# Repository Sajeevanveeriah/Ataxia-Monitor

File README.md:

# Ataxia Device and Monitor

This repository contains the VW-MTC1 MazeTrack controller design, its LTspice analysis tools, and the Android monitoring prototype. The controller package is the current hardware setup. The Android app still reads phone sensors; a board-to-app transport and executable board firmware have not been implemented.

## Project map

| Path | Contents |
| --- | --- |
| `VW-MTC1/Hardware/` | KiCad 10 sources, fabrication exports and archived ERC/DRC reports |
| `VW-MTC1/Firmware/` | ESP32-S3 pin-map header; no flashable firmware application yet |
| `VW-MTC1/Simulation/` | LTspice circuits, archived results/plots and Python analysis tools |
| `VW-MTC1/Docs/` | Original Rev00 design report, datasheet and images |
| `app/` | Android app, local JVM tests and [app documentation](app/README.md) |
| `tests/` | Python unit tests using synthetic waveforms and mocked simulator processes |
| `scripts/check_project.py` | Rebuild generated schematics and summary in `build/` |

The board has not been physically built or measured. Saved simulation and CAD reports are historical evidence, not a fresh hardware acceptance result. See [VW-MTC1/README.md](VW-MTC1/README.md) and the design report for outstanding engineering checks.

## Python build and tests from a clean checkout

Use Python 3.12 or newer. The development dependency set is pinned in `requirements-dev.txt`. NumPy 2 or newer is required because the analysis uses `numpy.trapezoid`.

Windows PowerShell:

```powershell
python -m venv .venv
.\.venv\Scripts\python.exe -m pip install -r requirements-dev.txt
.\.venv\Scripts\python.exe -m pip install --no-build-isolation -e .
.\.venv\Scripts\python.exe -m pytest -q
.\.venv\Scripts\python.exe -m build --no-isolation
.\.venv\Scripts\python.exe scripts/check_project.py
```

Linux/macOS:

```sh
python3 -m venv .venv
.venv/bin/python -m pip install -r requirements-dev.txt
.venv/bin/python -m pip install --no-build-isolation -e .
.venv/bin/python -m pytest -q
.venv/bin/python -m build --no-isolation
.venv/bin/python scripts/check_project.py
```

The build produces a Python wheel and source archive in `dist/`. It packages the tools, not the large hardware exports. The generation check writes to `build/vw-mtc1/` and preserves the supplied simulation evidence. Its summary is rebuilt from stored results; it does not claim a fresh simulation.

For line and branch coverage:

```sh
python -m pytest --cov=vw_mtc1 --cov-report=term-missing
```

Coverage reports include the full analysis scripts as well as the reusable helpers. Hardware-free unit tests do not execute every full-circuit analysis path.

A host C++ syntax check for the pin-map header is also available:

```sh
g++ -std=c++17 -Wall -Wextra -Werror -fsyntax-only tests/pinmap_compile.cpp
```

This checks header compilation only. It does not produce ESP32 firmware.

## Running LTspice

LTspice 26.1.1 was used for the supplied Rev00 evidence. Install LTspice separately, with its standard model library. No simulator is needed for the unit tests or Python package build.

The runner accepts `--executable`, then checks `LTSPICE_EXE`, `PATH` and standard Windows installation locations. It returns a failure for a timeout, a non-zero simulator exit, missing/unchanged/empty logs, simulator errors or failed measurements.

Run against a scratch copy when retaining the original logs:

```powershell
Copy-Item -Recurse VW-MTC1\Simulation\LTspice build\ltspice-run
.\.venv\Scripts\python.exe -m vw_mtc1.runlt build\ltspice-run\sim00_mosfet_model_check.cir 300
```

The source package omits raw waveform files. Regenerate the required `.cir` files before running `an_sim01` through `an_sim06_07`. Set `VW_MTC1_SIMULATION_DIR` to the scratch simulation directory containing `LTspice/`, `results.json` and, when generated, `Plots/`:

```powershell
$env:VW_MTC1_SIMULATION_DIR = (Resolve-Path build\vw-mtc1).Path
.\.venv\Scripts\python.exe -m vw_mtc1.an_sim01
```

The scripts execute sequentially when updating the same `results.json`; concurrent writers are not supported. Analysis modules should be run with `python -m vw_mtc1.<module>` after installation. A wheel installed outside this checkout also needs `VW_MTC1_SIMULATION_DIR` for data-dependent commands.

The five formerly timed-out cases completed with an 1800-second limit. Charger and
touch-gap investigations, diagnostic netlists and remaining acceptance failures are
documented in the [Rev01 verification record](docs/20261020-VW-MTC1-Verification-Rev01.md).
To reproduce the additional diagnostic sweeps:

```powershell
.\.venv\Scripts\python.exe scripts/investigate_analogue.py --output build\analogue-investigation --timeout 600
```

Simulation completion does not imply that every measurement or design target
passes. The runner also rejects failed rows in stepped measurement tables.

## Android build and tests

Use JDK 17, Android SDK platform 34 and build-tools 34.0.0. Set `JAVA_HOME` and `ANDROID_HOME` to those installations, or configure the SDK in Android Studio. The committed Gradle 8.2.1 wrapper verifies its distribution checksum.

```powershell
.\gradlew.bat assembleDebug testDebugUnitTest lintDebug
```

On Linux/macOS, use `./gradlew` with the same tasks. The debug APK is written to `app/build/outputs/apk/debug/`. JVM tests mock Android sensors and Room boundaries; they do not require a phone or emulator. Device instrumentation and physical sensor validation remain separate checks.

The app preserves raw phone proximity readings in their own sensor type. They are not calibrated along-maze distance. External board samples need an explicit transport and calibration contract before they can drive distance/offset fusion.

## Automated verification

The PR workflow builds and tests the Python tools on Windows and Linux, checks the pin-map header on Linux, and builds/tests/lints Android on Linux. It does not flash hardware, run physical measurements or regenerate fabrication exports.

The original thesis and previously delivered package ZIP remain local and are excluded from Git. The original Rev00 package files under `VW-MTC1/` remain available alongside the maintained source tools.

## Project handoff

Read the [project handoff](HANDOFF.md) for current work, checks and the next step.

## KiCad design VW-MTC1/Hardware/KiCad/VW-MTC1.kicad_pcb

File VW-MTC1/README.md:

# Voltwyn VW-MTC1 MazeTrack Controller - Rev A (Rev00 package, 19 October 2026)

Replacement controller board for the SEJ446 wire-maze ataxia assessment rig.

| Folder | Contents |
|---|---|
| `Docs/` | Datasheet PDF, design report PDF, schematic PDF, `Images/` (3D renders, layer plots, schematic PNGs) |
| `Hardware/KiCad/` | KiCad 10 project (open `VW-MTC1.kicad_pro`); custom symbol `Voltwyn.kicad_sym`, custom rules `VW-MTC1.kicad_dru` |
| `Hardware/Fabrication/` | Gerbers + drill (ZIP), BOM (CSV), pick-and-place (CSV), STEP 3D model |
| `Hardware/Reports/` | KiCad ERC and DRC reports |
| `Simulation/` | LTspice netlists and `.asc` schematics, plots, `results.json`, `Simulation_Summary.md` (raw waveform files not included: re-run the `.cir` files in LTspice to regenerate) |
| `Firmware/` | `vw_mtc1_pins.h` ESP32-S3 pin map |

Status: design complete, ERC 0 errors, DRC 0 errors / 0 unconnected / 0 schematic-parity issues.
Not yet built or measured. See the open items in section 10 of the design report before ordering.
Research and education use only; not a registered medical device.

The table and status above describe the original Rev00 design package. The maintained
Python tools now have a package build and hardware-free regression suite. See the
[repository build instructions](../README.md) and
[latest verification record](../docs/20261020-VW-MTC1-Verification-Rev01.md).
`Firmware/` still contains a pin-map header only, not a flashable firmware application.

## Project handoff

Read the [project handoff](../HANDOFF.md) for current work, checks and the next step.

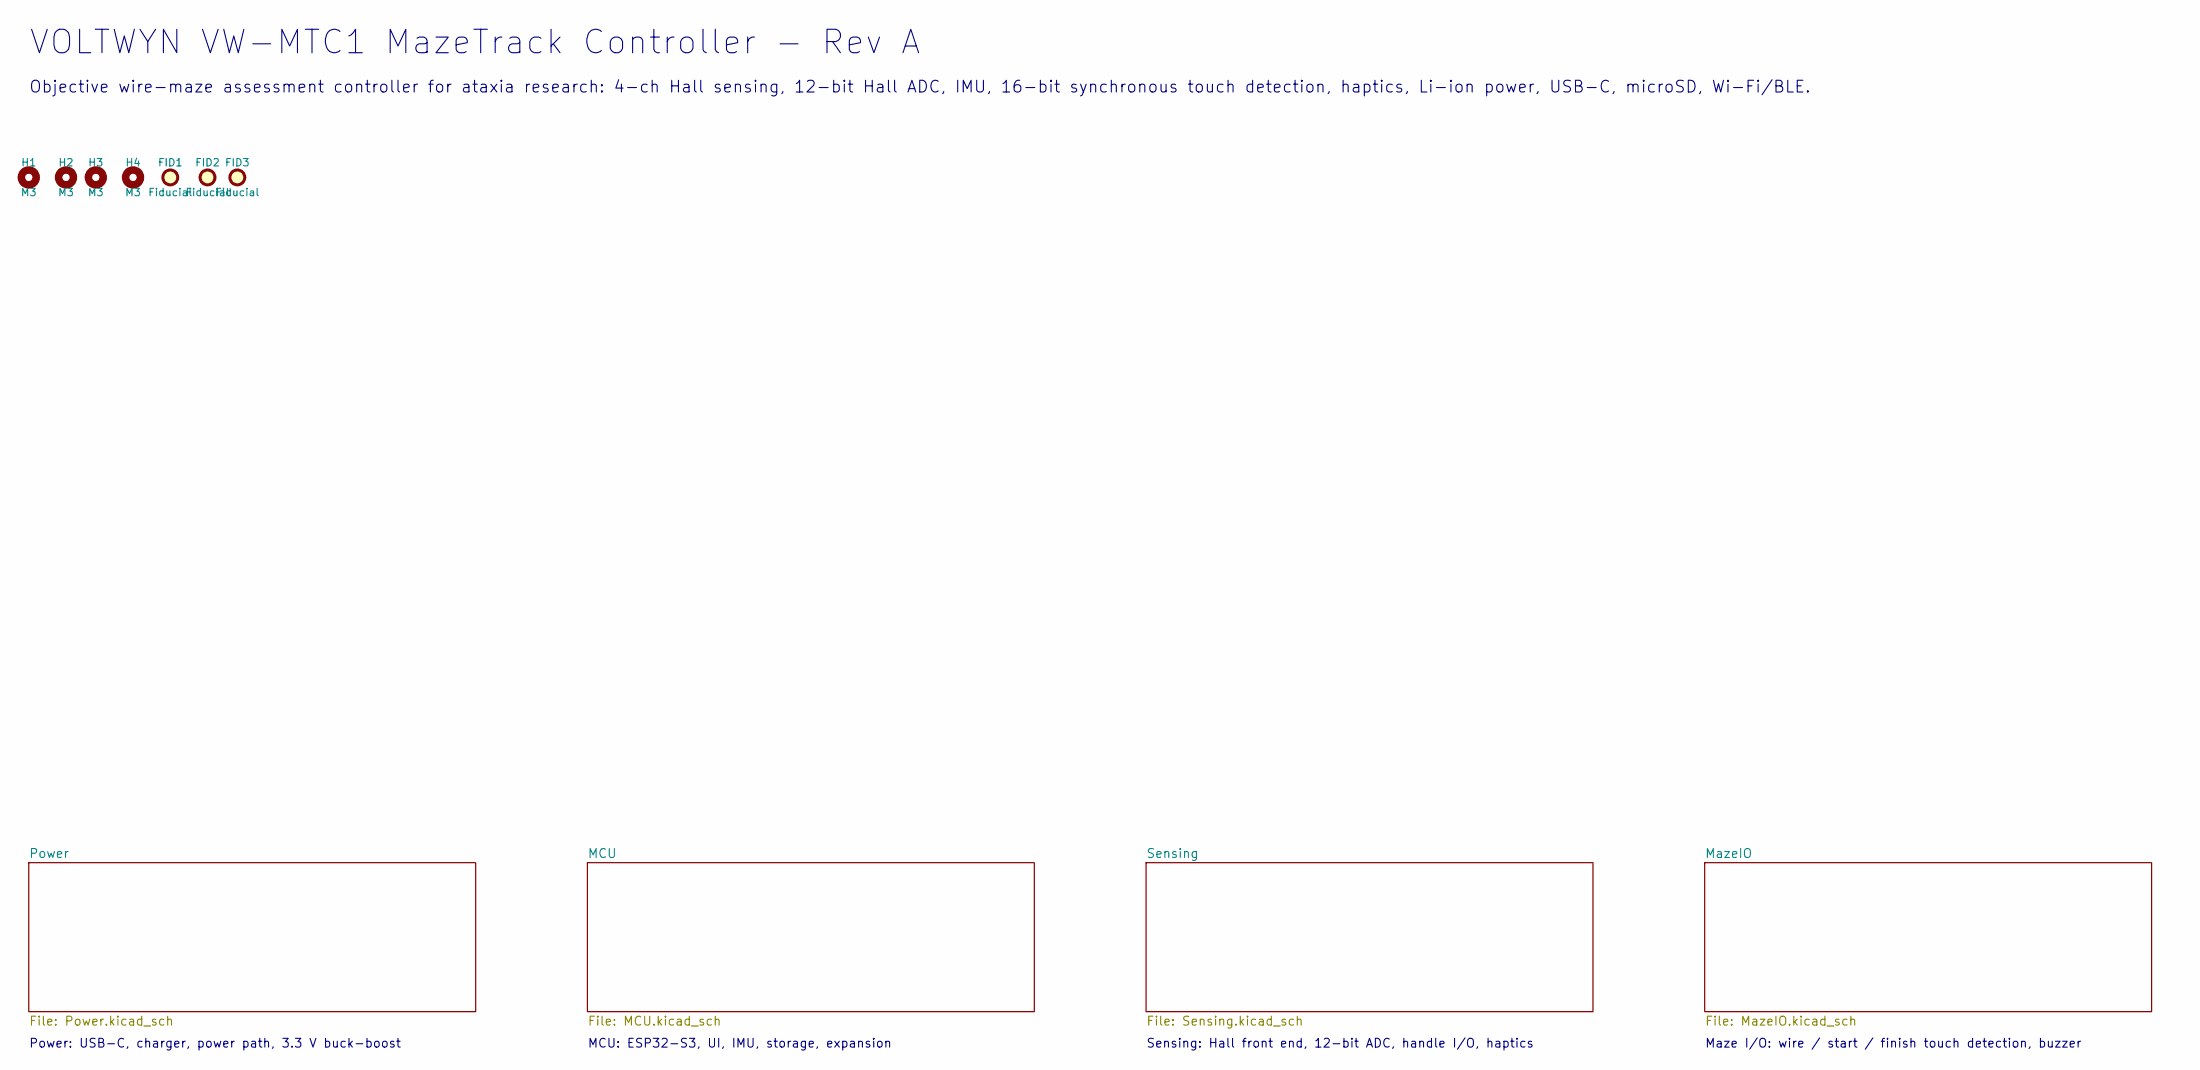
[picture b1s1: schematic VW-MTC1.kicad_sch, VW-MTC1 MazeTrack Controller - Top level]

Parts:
FID1, FID2, FID3: Fiducial; Fiducial_1mm_Mask2mm
H1, H2, H3, H4: M3; MountingHole_3.2mm_M3

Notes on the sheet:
VOLTWYN VW-MTC1 MazeTrack Controller - Rev A
Objective wire-maze assessment controller for ataxia research: 4-ch Hall sensing, 12-bit Hall ADC, IMU, 16-bit synchronous touch detection, haptics, Li-ion power, USB-C, microSD, Wi-Fi/BLE.
Power: USB-C, charger, power path, 3.3 V buck-boost
MCU: ESP32-S3, UI, IMU, storage, expansion
Sensing: Hall front end, 12-bit ADC, handle I/O, haptics
Maze I/O: wire / start / finish touch detection, buzzer

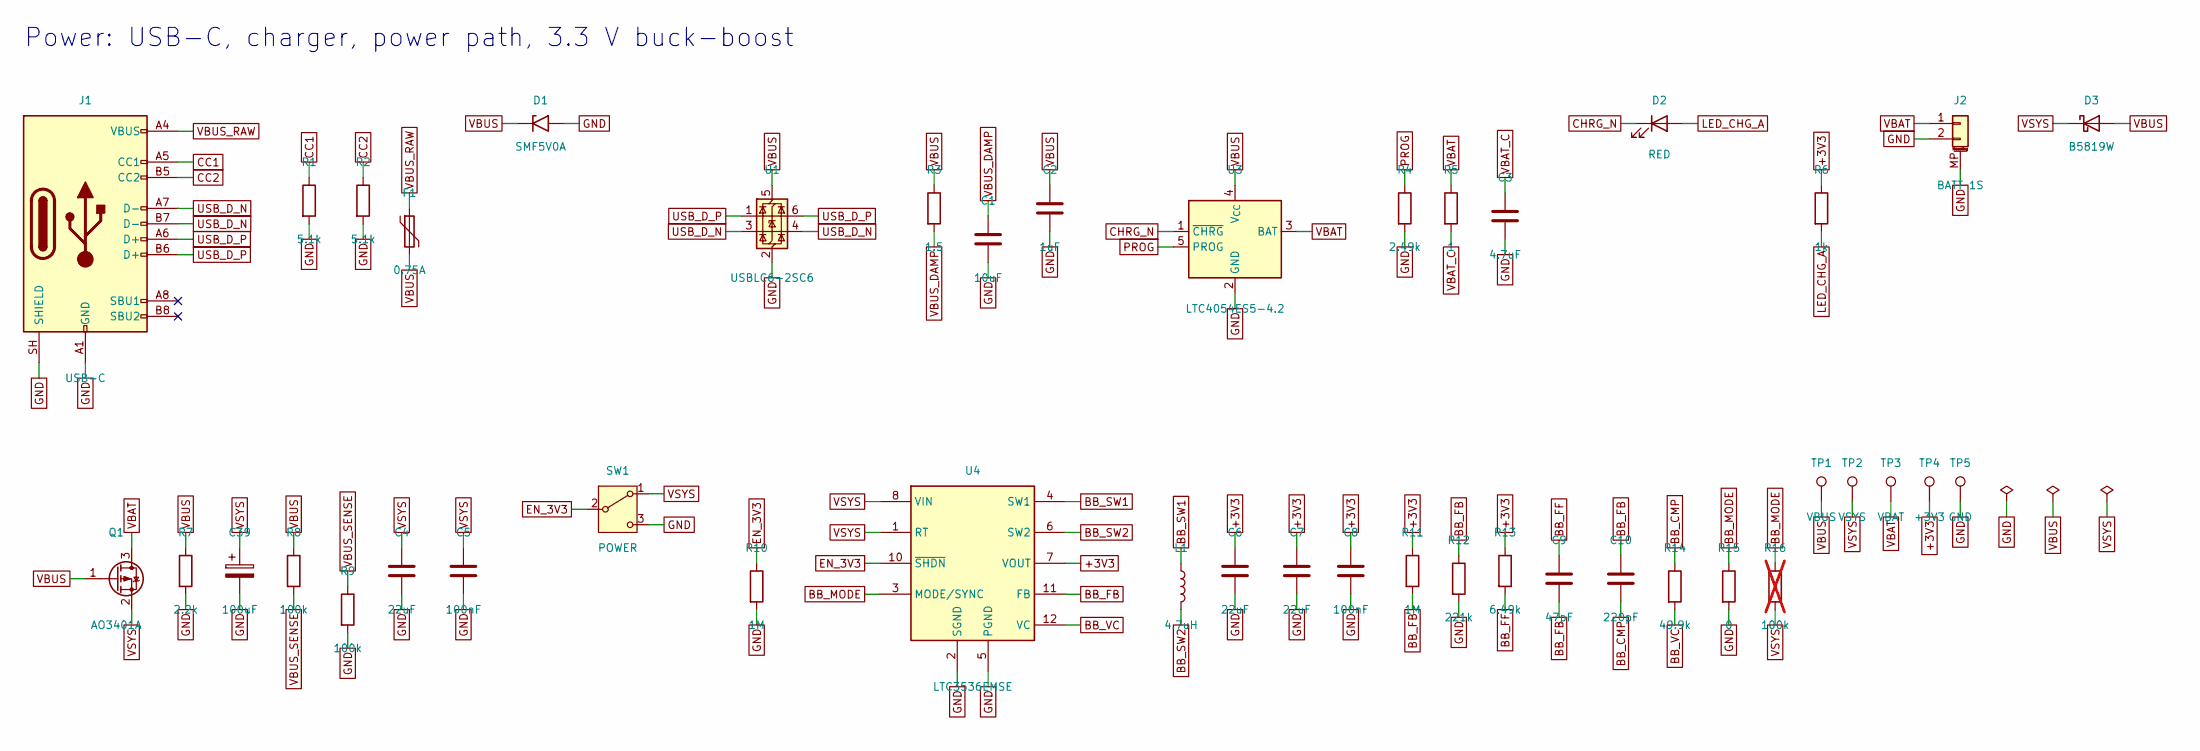
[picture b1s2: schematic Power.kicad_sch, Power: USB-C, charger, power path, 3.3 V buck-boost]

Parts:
C1: 10uF; C_0805_2012Metric; MPN GRM21BR61E106KA73L
C2: 1uF; C_0603_1608Metric; MPN GRM188R61E105KA12D
C3: 4.7uF; C_0805_2012Metric; MPN GRM21BR61C475KA88L
C4, C6, C7: 22uF; C_0805_2012Metric; MPN GRM21BR61A226ME44L
C5, C8: 100nF; C_0603_1608Metric; MPN GRM188R71H104KA93D
C9: 47pF; C_0603_1608Metric; MPN GRM1885C1H470JA01D
C10: 220pF; C_0603_1608Metric; MPN GRM1885C1H221JA01D
C39: 100uF; CP_EIA-3528-21_Kemet-B; MPN T520B107M006ATE070
D1: SMF5V0A; D_SMF; MPN SMF5V0A
D2: RED; LED_0603_1608Metric; MPN 150060RS75000
D3: B5819W; D_SOD-123; MPN B5819W
F1: 0.75A; Fuse_1206_3216Metric; MPN 1206L075THYR
J1: USB-C; USB_C_Receptacle_GCT_USB4105-xx-A_16P_TopMnt_Horizontal; MPN USB4105-GF-A
J2: BATT 1S; JST_PH_S2B-PH-SM4-TB_1x02-1MP_P2.00mm_Horizontal; MPN S2B-PH-SM4-TB(LF)(SN)
L1: 4.7uH; L_Coilcraft_XxL4020; MPN XFL4020-472MEC
Q1: AO3401A; SOT-23; MPN AO3401A
R1, R2: 5.1k; R_0603_1608Metric; MPN RC0603FR-075R1kL
R3: 1.5; R_0603_1608Metric; MPN RC0603FR-071R5L
R4: 2.49k; R_0603_1608Metric; MPN RC0603FR-072K49L
R5: 1; R_0603_1608Metric; MPN RC0603FR-071RL
R6: 1k; R_0603_1608Metric; MPN RC0603FR-071kL
R7: 2.2k; R_0603_1608Metric; MPN RC0603FR-072R2kL
R8, R9: 100k; R_0603_1608Metric; MPN RC0603FR-07100kL
R10, R11: 1M; R_0603_1608Metric; MPN RC0603FR-071ML
R12: 221k; R_0603_1608Metric; MPN RC0603FR-07221kL
R13: 6.49k; R_0603_1608Metric; MPN RC0603FR-076R49kL
R14: 49.9k; R_0603_1608Metric; MPN RC0603FR-0749R9kL
R15: 0; R_0603_1608Metric; MPN RC0603JR-070RL
R16: 100k; R_0603_1608Metric; MPN RC0603FR-07100kL; not fitted
SW1: POWER; SW_SPDT_PCM12; MPN PCM12SMTR
TP1: VBUS; TestPoint_Pad_D1.5mm
TP2: VSYS; TestPoint_Pad_D1.5mm
TP3: VBAT; TestPoint_Pad_D1.5mm
TP4: +3V3; TestPoint_Pad_D1.5mm
TP5: GND; TestPoint_Pad_D1.5mm
U1: USBLC6-2SC6; SOT-23-6; MPN USBLC6-2SC6
U3: LTC4054ES5-4.2; TSOT-23-5; MPN LTC4054ES5-4.2#TRPBF
U4: LTC3536EMSE; MSOP-12-1EP_3x4.039mm_P0.65mm_EP1.651x2.845mm_ThermalVias; MPN LTC3536EMSE#PBF

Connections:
+3V3: C6.1, C7.1, C8.1, R6.1, R11.1, R13.1, TP4.1, U4.7 (VOUT); also elsewhere on the board
BB_CMP: C10.2, R14.1
BB_FB: C9.2, C10.1, R11.2, R12.1, U4.11 (FB)
BB_FF: C9.1, R13.2
BB_MODE: R15.1, R16.1, U4.3 (MODE/SYNC)
BB_SW1: L1.1, U4.4 (SW1)
BB_SW2: L1.2, U4.6 (SW2)
BB_VC: R14.2, U4.12 (VC)
CC1: J1.A5 (CC1), R1.1
CC2: J1.B5 (CC2), R2.1
CHRG_N: D2.1 (K), U3.1 (~CHRG); also elsewhere on the board
EN_3V3: R10.1, SW1.2 (B), U4.10 (~SHDN)
GND: C1.2, C2.2, C3.2, C4.2, C5.2, C6.2, C7.2, C8.2, C39.2, D1.2 (A2), J1.A1 (GND), J1.A12 (GND), J1.B1 (GND), J1.B12 (GND), J1.SH (SHIELD), J2.2, J2.MP (MountPin), R1.2, R2.2, R4.2, R7.2, R9.2, R10.2, R12.2, R15.2, SW1.3 (C), TP5.1, U1.2 (GND), U3.2 (GND), U4.2 (SGND), U4.5 (PGND), U4.13 (PGND); also elsewhere on the board
LED_CHG_A: D2.2 (A), R6.2
PROG: R4.1, U3.5 (PROG)
USB_D_N: J1.A7 (D-), J1.B7 (D-), U1.3 (I/O2), U1.4 (I/O2); also elsewhere on the board
USB_D_P: J1.A6 (D+), J1.B6 (D+), U1.1 (I/O1), U1.6 (I/O1); also elsewhere on the board
VBAT: J2.1, Q1.3 (D), R5.1, TP3.1, U3.3 (BAT); also elsewhere on the board
VBAT_C: C3.1, R5.2
VBUS: C2.1, D1.1 (A1), D3.2 (A), F1.2, Q1.1 (G), R3.1, R7.1, R8.1, TP1.1, U1.5 (VBUS), U3.4 (V_{CC})
VBUS_DAMP: C1.1, R3.2
VBUS_RAW: F1.1, J1.A4 (VBUS), J1.A9 (VBUS), J1.B4 (VBUS), J1.B9 (VBUS)
VBUS_SENSE: R8.2, R9.1; also elsewhere on the board
VSYS: C4.1, C5.1, C39.1, D3.1 (K), Q1.2 (S), R16.2, SW1.1 (A), TP2.1, U4.1 (RT), U4.8 (VIN), U4.9 (VIN); also elsewhere on the board

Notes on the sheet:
Power: USB-C, charger, power path, 3.3 V buck-boost

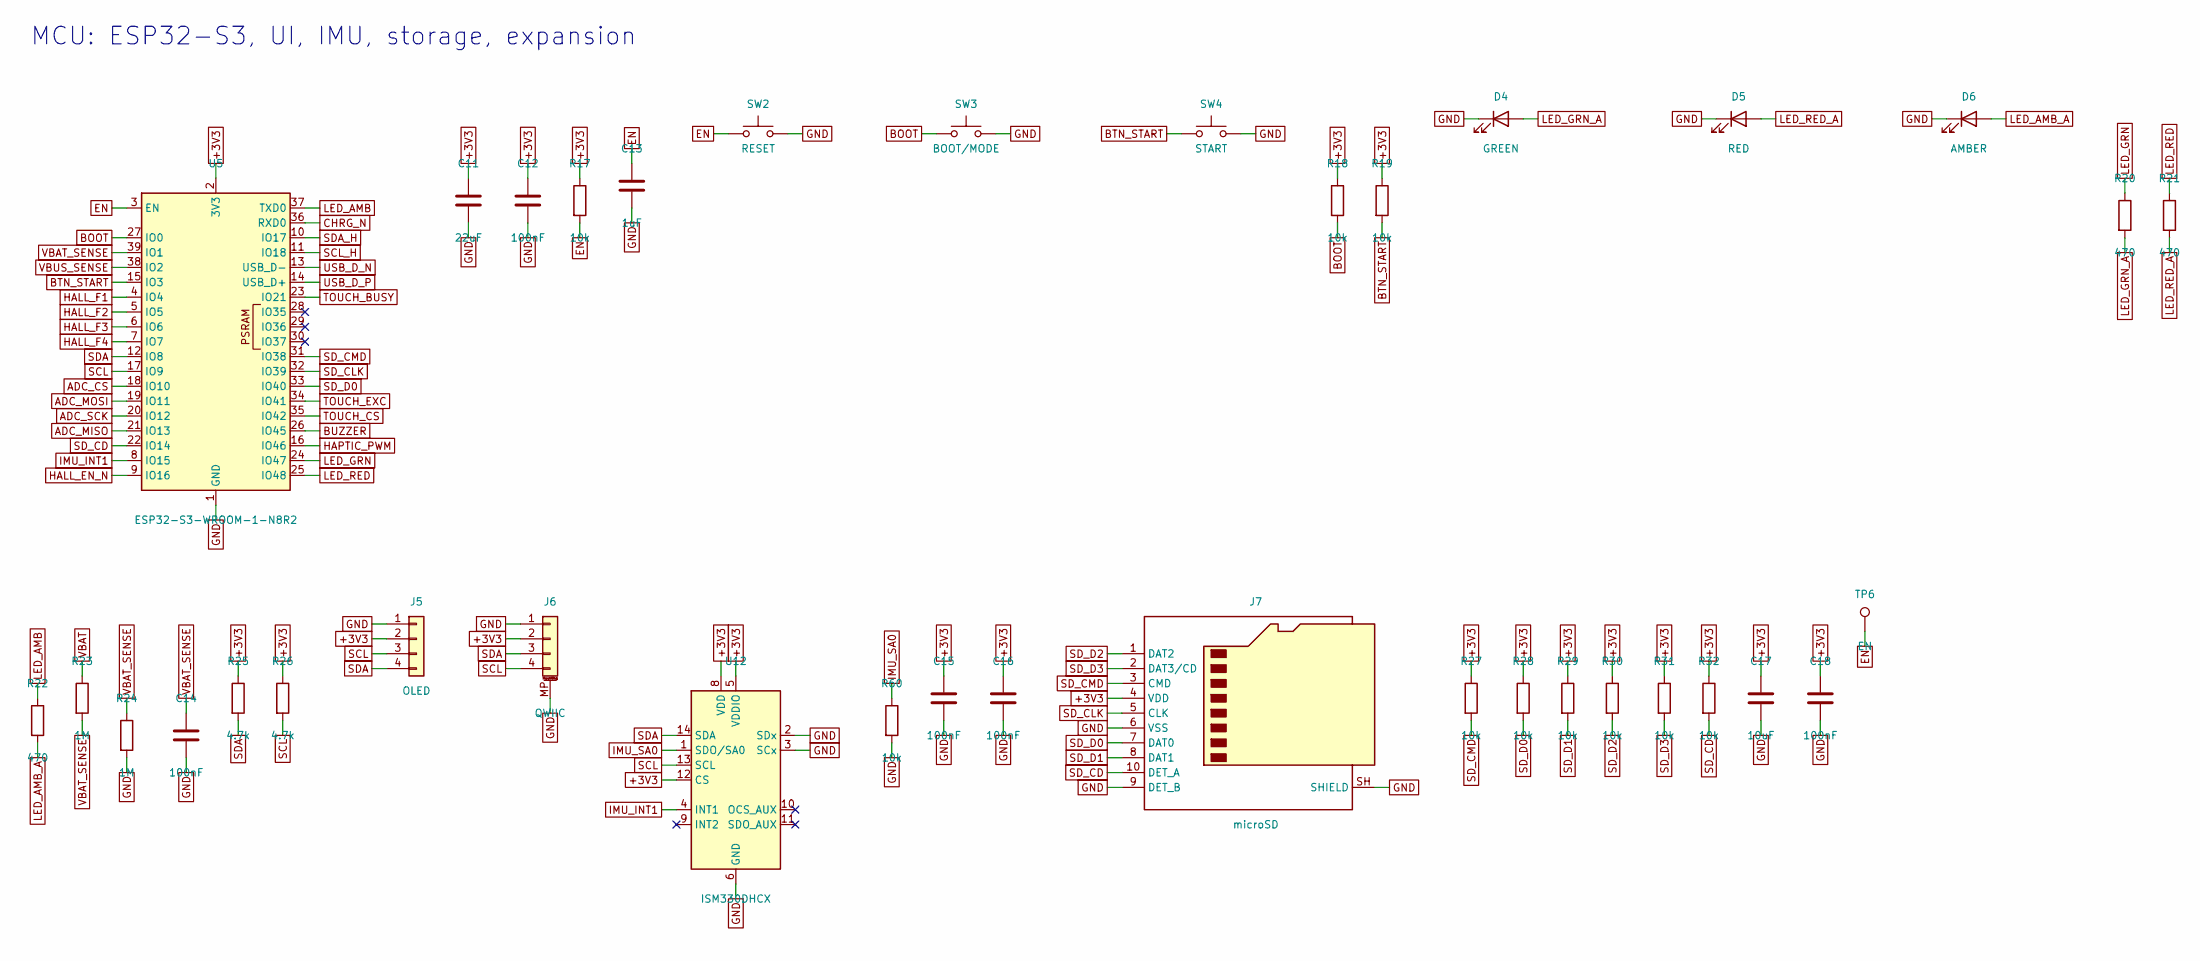
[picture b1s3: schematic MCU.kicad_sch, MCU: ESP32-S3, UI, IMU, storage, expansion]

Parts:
C11: 22uF; C_0805_2012Metric; MPN GRM21BR61A226ME44L
C12, C14, C15, C16, C18: 100nF; C_0603_1608Metric; MPN GRM188R71H104KA93D
C13: 1uF; C_0603_1608Metric; MPN GRM188R61E105KA12D
C17: 10uF; C_0805_2012Metric; MPN GRM21BR61E106KA73L
D4: GREEN; LED_0603_1608Metric; MPN 150060GS75000
D5: RED; LED_0603_1608Metric; MPN 150060RS75000
D6: AMBER; LED_0603_1608Metric; MPN 150060AS75000
J5: OLED; PinHeader_1x04_P2.54mm_Vertical; MPN PH1-04-UA
J6: QWIIC; JST_SH_SM04B-SRSS-TB_1x04-1MP_P1.00mm_Horizontal; MPN SM04B-SRSS-TB(LF)(SN)
J7: microSD; microSD_HC_Hirose_DM3AT-SF-PEJM5; MPN DM3AT-SF-PEJM5
R17, R18, R19, R27, R28, R29, R30, R31, R32, R60: 10k; R_0603_1608Metric; MPN RC0603FR-0710kL
R20, R21, R22: 470; R_0603_1608Metric; MPN RC0603FR-07470L
R23, R24: 1M; R_0603_1608Metric; MPN RC0603FR-071ML
R25, R26: 4.7k; R_0603_1608Metric; MPN RC0603FR-074R7kL
SW2: RESET; SW_SPST_TL3342; MPN TL3342F160QG
SW3: BOOT/MODE; SW_SPST_TL3342; MPN TL3342F160QG
SW4: START; SW_SPST_TL3342; MPN TL3342F160QG
TP6: EN; TestPoint_Pad_D1.5mm
U5: ESP32-S3-WROOM-1-N8R2; ESP32-S3-WROOM-1; MPN ESP32-S3-WROOM-1-N8R2
U12: ISM330DHCX; LGA-14_3x2.5mm_P0.5mm_LayoutBorder3x4y; MPN ISM330DHCXTR

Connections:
+3V3: C11.1, C12.1, C15.1, C16.1, C17.1, C18.1, J5.2, J6.2, J7.4 (VDD), R17.1, R18.1, R19.1, R25.1, R26.1, R27.1, R28.1, R29.1, R30.1, R31.1, R32.1, U5.2 (3V3), U12.5 (VDDIO), U12.8 (VDD), U12.12 (CS); also elsewhere on the board
ADC_CS: U5.18 (IO10); also elsewhere on the board
ADC_MISO: U5.21 (IO13); also elsewhere on the board
ADC_MOSI: U5.19 (IO11); also elsewhere on the board
ADC_SCK: U5.20 (IO12); also elsewhere on the board
BOOT: R18.2, SW3.1, U5.27 (IO0)
BTN_START: R19.2, SW4.1, U5.15 (IO3)
BUZZER: U5.26 (IO45); also elsewhere on the board
CHRG_N: U5.36 (RXD0); also elsewhere on the board
EN: C13.1, R17.2, SW2.1, TP6.1, U5.3 (EN)
GND: C11.2, C12.2, C13.2, C14.2, C15.2, C16.2, C17.2, C18.2, D4.1 (K), D5.1 (K), D6.1 (K), J5.1, J6.1, J6.MP (MountPin), J7.6 (VSS), J7.9 (DET_B), J7.SH (SHIELD), R24.2, R60.2, SW2.2, SW3.2, SW4.2, U5.1 (GND), U5.40 (GND), U5.41 (GND), U12.2 (SDx), U12.3 (SCx), U12.6 (GND), U12.7 (GND); also elsewhere on the board
HALL_EN_N: U5.9 (IO16); also elsewhere on the board
HALL_F1: U5.4 (IO4); also elsewhere on the board
HALL_F2: U5.5 (IO5); also elsewhere on the board
HALL_F3: U5.6 (IO6); also elsewhere on the board
HALL_F4: U5.7 (IO7); also elsewhere on the board
HAPTIC_PWM: U5.16 (IO46); also elsewhere on the board
IMU_INT1: U5.8 (IO15), U12.4 (INT1)
IMU_SA0: R60.1, U12.1 (SDO/SA0)
LED_AMB: R22.1, U5.37 (TXD0)
LED_AMB_A: D6.2 (A), R22.2
LED_GRN: R20.1, U5.24 (IO47)
LED_GRN_A: D4.2 (A), R20.2
LED_RED: R21.1, U5.25 (IO48)
LED_RED_A: D5.2 (A), R21.2
SCL: J5.3, J6.4, R26.2, U5.17 (IO9), U12.13 (SCL)
SCL_H: U5.11 (IO18); also elsewhere on the board
SDA: J5.4, J6.3, R25.2, U5.12 (IO8), U12.14 (SDA)
SDA_H: U5.10 (IO17); also elsewhere on the board
SD_CD: J7.10 (DET_A), R32.2, U5.22 (IO14)
SD_CLK: J7.5 (CLK), U5.32 (IO39)
SD_CMD: J7.3 (CMD), R27.2, U5.31 (IO38)
SD_D0: J7.7 (DAT0), R28.2, U5.33 (IO40)
SD_D1: J7.8 (DAT1), R29.2
SD_D2: J7.1 (DAT2), R30.2
SD_D3: J7.2 (DAT3/CD), R31.2
TOUCH_BUSY: U5.23 (IO21); also elsewhere on the board
TOUCH_CS: U5.35 (IO42); also elsewhere on the board
TOUCH_EXC: U5.34 (IO41); also elsewhere on the board
USB_D_N: U5.13 (USB_D-); also elsewhere on the board
USB_D_P: U5.14 (USB_D+); also elsewhere on the board
VBAT: R23.1; also elsewhere on the board
VBAT_SENSE: C14.1, R23.2, R24.1, U5.39 (IO1)
VBUS_SENSE: U5.38 (IO2); also elsewhere on the board

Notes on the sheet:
MCU: ESP32-S3, UI, IMU, storage, expansion

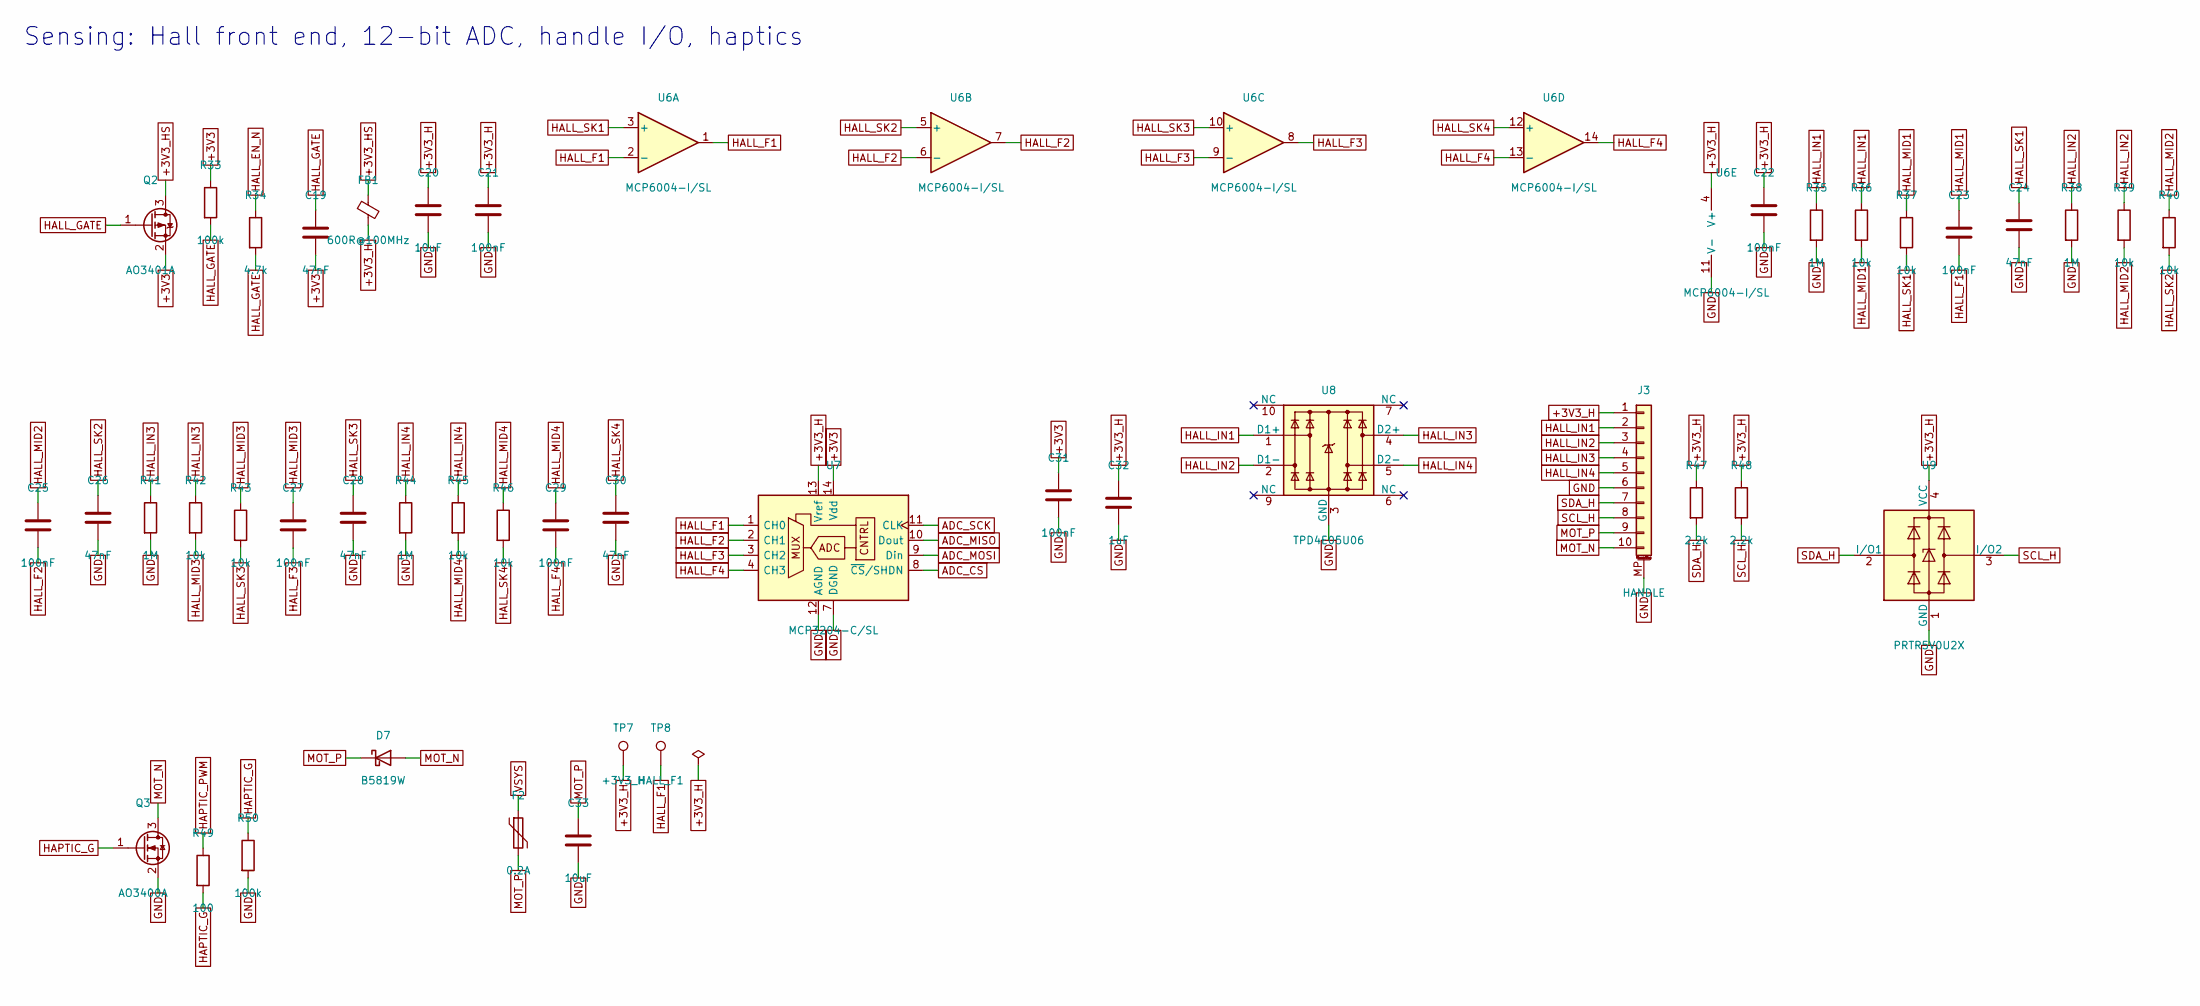
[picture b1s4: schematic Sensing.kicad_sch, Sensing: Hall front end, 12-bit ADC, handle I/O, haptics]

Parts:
C19: 47nF; C_0603_1608Metric; MPN GRM188R71H473KA61D
C20, C33: 10uF; C_0805_2012Metric; MPN GRM21BR61E106KA73L
C21, C22, C31: 100nF; C_0603_1608Metric; MPN GRM188R71H104KA93D
C23, C25, C27, C29: 100nF; C_0805_2012Metric; MPN GCM21B5C1H104JA16L
C24, C26, C28, C30: 47nF; C_0805_2012Metric; MPN GRM2195C1H473JA01D
C32: 1uF; C_0603_1608Metric; MPN GRM188R61E105KA12D
D7: B5819W; D_SOD-123; MPN B5819W
F2: 0.2A; Fuse_0805_2012Metric; MPN 0805L020WR
FB1: 600R@100MHz; L_0603_1608Metric; MPN BLM18PG601SN1D
J3: HANDLE; JST_GH_SM10B-GHS-TB_1x10-1MP_P1.25mm_Horizontal; MPN SM10B-GHS-TB(LF)(SN)
Q2: AO3401A; SOT-23; MPN AO3401A
Q3: AO3400A; SOT-23; MPN AO3400A
R33, R50: 100k; R_0603_1608Metric; MPN RC0603FR-07100kL
R34: 4.7k; R_0603_1608Metric; MPN RC0603FR-074R7kL
R35, R38, R41, R44: 1M; R_0603_1608Metric; MPN RC0603FR-071ML
R36, R37, R39, R40, R42, R43, R45, R46: 10k; R_0603_1608Metric; MPN RC0603FR-0710kL
R47, R48: 2.2k; R_0603_1608Metric; MPN RC0603FR-072R2kL
R49: 100; R_0603_1608Metric; MPN RC0603FR-07100L
TP7: +3V3_H; TestPoint_Pad_D1.5mm
TP8: HALL_F1; TestPoint_Pad_D1.5mm
U6: MCP6004-I/SL; SOIC-14_3.9x8.7mm_P1.27mm; MPN MCP6004T-I/SL
U7: MCP3204-C/SL; SOIC-14_3.9x8.7mm_P1.27mm; MPN MCP3204-CI/SL
U8: TPD4E05U06; USON-10_2.5x1.0mm_P0.5mm; MPN TPD4E05U06DQAR
U9: PRTR5V0U2X; SOT-143; MPN PRTR5V0U2X,215

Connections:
+3V3: C19.2, C31.1, Q2.2 (S), R33.1, U7.14 (Vdd); also elsewhere on the board
+3V3_H: C20.1, C21.1, C22.1, C32.1, FB1.2, J3.1, R47.1, R48.1, TP7.1, U6.4 (V+), U7.13 (Vref), U9.4 (VCC)
+3V3_HS: FB1.1, Q2.3 (D)
ADC_CS: U7.8 (~CS/SHDN); also elsewhere on the board
ADC_MISO: U7.10 (Dout); also elsewhere on the board
ADC_MOSI: U7.9 (Din); also elsewhere on the board
ADC_SCK: U7.11 (CLK); also elsewhere on the board
GND: C20.2, C21.2, C22.2, C24.2, C26.2, C28.2, C30.2, C31.2, C32.2, C33.2, J3.6, J3.MP (MountPin), Q3.2 (S), R35.2, R38.2, R41.2, R44.2, R50.2, U6.11 (V-), U7.7 (DGND), U7.12 (AGND), U8.3 (GND), U8.8 (GND), U9.1 (GND); also elsewhere on the board
HALL_EN_N: R34.1; also elsewhere on the board
HALL_F1: C23.2, TP8.1, U6.1, U6.2 (-), U7.1 (CH0); also elsewhere on the board
HALL_F2: C25.2, U6.6 (-), U6.7, U7.2 (CH1); also elsewhere on the board
HALL_F3: C27.2, U6.8, U6.9 (-), U7.3 (CH2); also elsewhere on the board
HALL_F4: C29.2, U6.13 (-), U6.14, U7.4 (CH3); also elsewhere on the board
HALL_GATE: C19.1, Q2.1 (G), R33.2, R34.2
HALL_IN1: J3.2, R35.1, R36.1, U8.1 (D1+)
HALL_IN2: J3.3, R38.1, R39.1, U8.2 (D1-)
HALL_IN3: J3.4, R41.1, R42.1, U8.4 (D2+)
HALL_IN4: J3.5, R44.1, R45.1, U8.5 (D2-)
HALL_MID1: C23.1, R36.2, R37.1
HALL_MID2: C25.1, R39.2, R40.1
HALL_MID3: C27.1, R42.2, R43.1
HALL_MID4: C29.1, R45.2, R46.1
HALL_SK1: C24.1, R37.2, U6.3 (+)
HALL_SK2: C26.1, R40.2, U6.5 (+)
HALL_SK3: C28.1, R43.2, U6.10 (+)
HALL_SK4: C30.1, R46.2, U6.12 (+)
HAPTIC_G: Q3.1 (G), R49.2, R50.1
HAPTIC_PWM: R49.1; also elsewhere on the board
MOT_N: D7.2 (A), J3.10, Q3.3 (D)
MOT_P: C33.1, D7.1 (K), F2.2, J3.9
SCL_H: J3.8, R48.2, U9.3 (I/O2); also elsewhere on the board
SDA_H: J3.7, R47.2, U9.2 (I/O1); also elsewhere on the board
VSYS: F2.1; also elsewhere on the board

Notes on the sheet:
Sensing: Hall front end, 12-bit ADC, handle I/O, haptics
